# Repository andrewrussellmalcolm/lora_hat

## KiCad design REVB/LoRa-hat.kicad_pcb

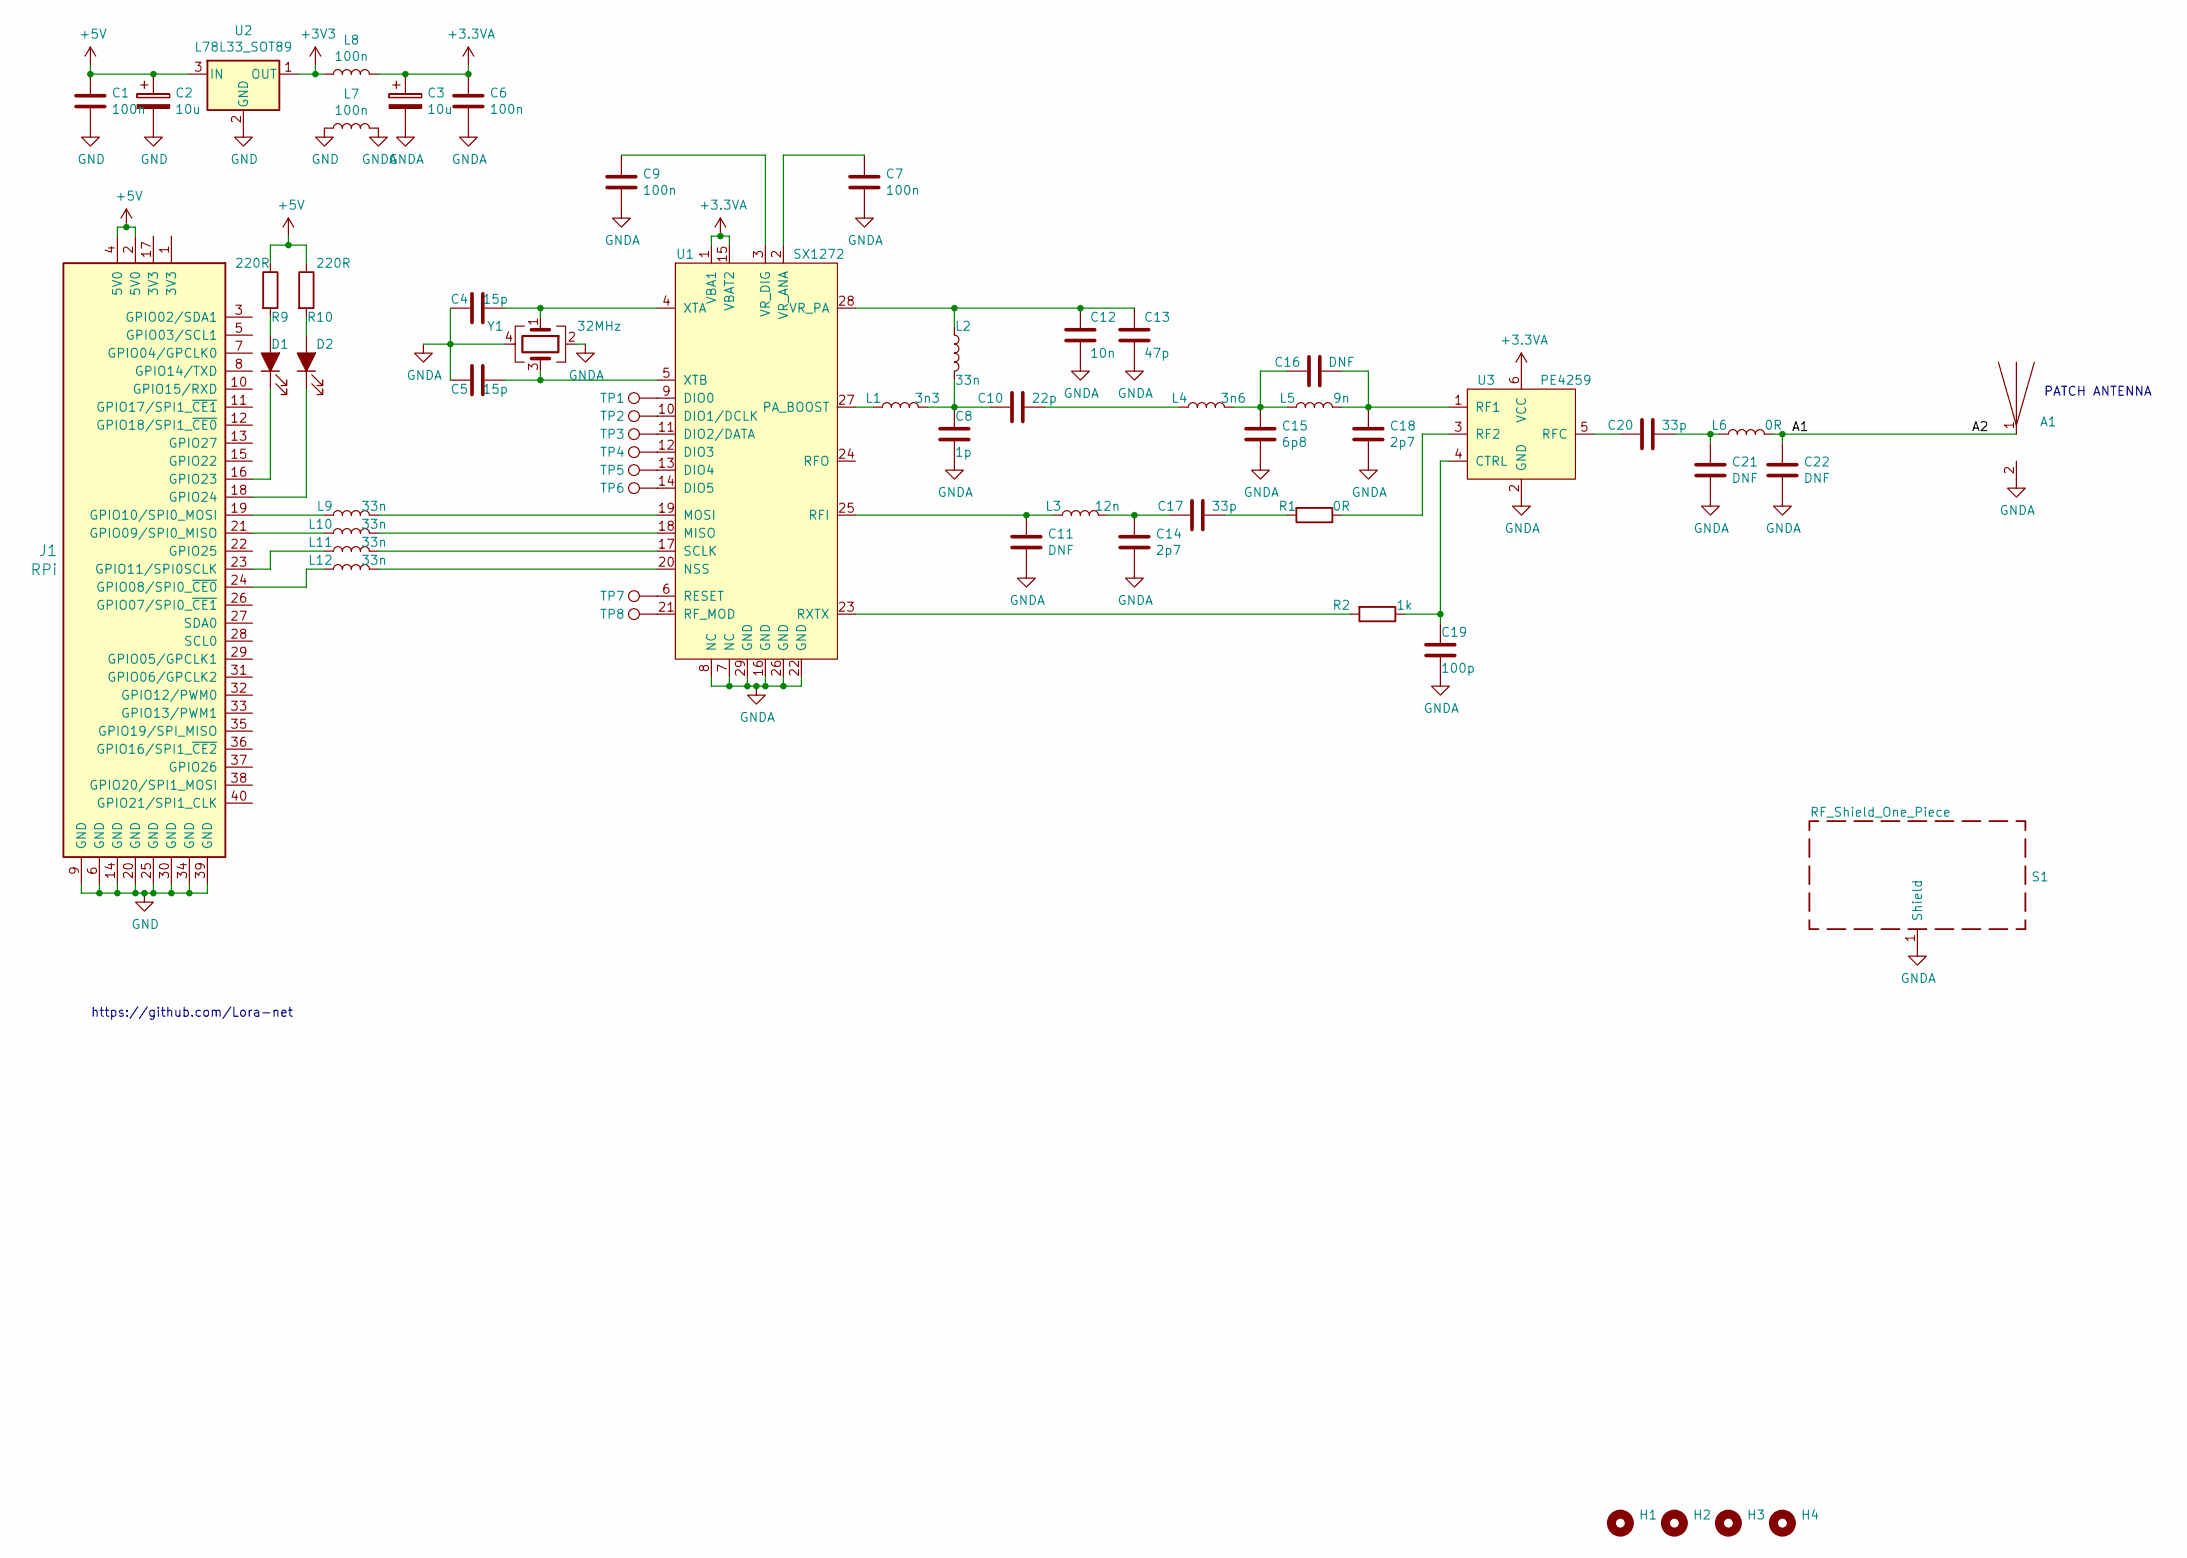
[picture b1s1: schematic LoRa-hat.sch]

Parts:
A1: F-ANTENNA-868MHz
C1, C6, C7, C9: 100n; C_0603_1608Metric
C2, C3: 10u; CP_EIA-3216-10_Kemet-I
C4, C5: 15p; C_0603_1608Metric
C8: 1p; C_0603_1608Metric
C10: 22p; C_0603_1608Metric
C11, C16, C21, C22: DNF; C_0603_1608Metric
C12: 10n; C_0603_1608Metric
C13: 47p; C_0603_1608Metric
C14, C18: 2p7; C_0603_1608Metric
C15: 6p8; C_0603_1608Metric
C17, C20: 33p; C_0603_1608Metric
C19: 100p; C_0603_1608Metric
D1, D2: LED_ALT; LED_LH_R974
H1, H2, H3, H4: Mechanical_Mounting_Hole; Mounting_hole_2.5mm
J1: RPi; PinSocket_2x20_P2.54mm_Vertical
L1: 3n3; L_0603_1608Metric
L2, L9, L10, L11, L12: 33n; L_0603_1608Metric
L3: 12n; L_0603_1608Metric
L4: 3n6; L_0603_1608Metric
L5: 9n; L_0603_1608Metric
L6: 0R; L_0603_1608Metric
L7, L8: 100n; L_0603_1608Metric
R1: 0R; R_0603_1608Metric
R2: 1k; R_0603_1608Metric
R9, R10: 220R; R_0603_1608Metric
S1: RF_Shield_One_Piece; MS256-10S
TP1, TP2, TP3, TP4, TP5, TP6, TP7, TP8: TestPoint; TestPoint_Pad_D1.0mm
U1: SX1272; QFN-28-1EP_6x6mm_P0.65mm_EP4.25x4.25mm_ThermalVias
U2: L78L33_SOT89; SOT-89-3
U3: PE4259; SC70-6
Y1: 32MHz; Crystal_SMD_2016-4Pin_2.0x1.6mm

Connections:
+3.3VA: C3.1, C6.1, L8.2, U1.1 (VBA1), U1.15 (VBAT2), U3.6 (VCC)
+3V3: L8.1, U2.1 (OUT)
+5V: C1.1, C2.1, J1.2 (5V0), J1.4 (5V0), R9.1, R10.1, U2.3 (IN)
/A1: A1.1, C22.1, L6.2
GND: C1.2, C2.2, J1.6 (GND), J1.9 (GND), J1.14 (GND), J1.20 (GND), J1.25 (GND), J1.30 (GND), J1.34 (GND), J1.39 (GND), L7.1, U2.2 (GND)
GNDA: A1.2, C3.2, C4.2, C5.2, C6.2, C7.2, C8.2, C9.2, C11.2, C12.2, C13.2, C14.2, C15.2, C18.2, C19.2, C21.2, C22.2, L7.2, S1.1, U1.7 (NC), U1.8 (NC), U1.16 (GND), U1.22 (GND), U1.26 (GND), U1.29 (GND), U3.2 (GND), Y1.2, Y1.4
unnamed: C4.1, U1.4 (XTA), Y1.1
unnamed: C5.1, U1.5 (XTB), Y1.3
unnamed: C7.1, U1.2 (VR_ANA)
unnamed: C9.1, U1.3 (VR_DIG)
unnamed: C10.1, L4.1
unnamed: C8.1, C10.2, L1.2, L2.2
unnamed: C11.1, L3.1, U1.25 (RFI)
unnamed: C12.1, C13.1, L2.1, U1.28 (VR_PA)
unnamed: C14.1, C17.2, L3.2
unnamed: C15.1, C16.2, L4.2, L5.1
unnamed: C16.1, C18.1, L5.2, U3.1 (RF1)
unnamed: C17.1, R1.2
unnamed: C19.1, R2.1, U3.4 (CTRL)
unnamed: C20.1, C21.1, L6.1
unnamed: C20.2, U3.5 (RFC)
unnamed: D1.1 (K), J1.16 (GPIO23)
unnamed: D1.2 (A), R9.2
unnamed: D2.1 (K), J1.18 (GPIO24)
unnamed: D2.2 (A), R10.2
unnamed: J1.19 (GPIO10/SPI0_MOSI), L9.1
unnamed: J1.21 (GPIO09/SPI0_MISO), L10.1
unnamed: J1.23 (GPIO11/SPI0SCLK), L11.1
unnamed: J1.24 (GPIO08/SPI0_~CE0), L12.1
unnamed: L1.1, U1.27 (PA_BOOST)
unnamed: L9.2, U1.19 (MOSI)
unnamed: L10.2, U1.18 (MISO)
unnamed: L11.2, U1.17 (SCLK)
unnamed: L12.2, U1.20 (NSS)
unnamed: R1.1, U3.3 (RF2)
unnamed: R2.2, U1.23 (RXTX)
unnamed: TP1.1, U1.9 (DIO0)
unnamed: TP2.1, U1.10 (DIO1/DCLK)
unnamed: TP3.1, U1.11 (DIO2/DATA)
unnamed: TP4.1, U1.12 (DIO3)
unnamed: TP5.1, U1.13 (DIO4)
unnamed: TP6.1, U1.14 (DIO5)
unnamed: TP7.1, U1.6 (RESET)
unnamed: TP8.1, U1.21 (RF_MOD)

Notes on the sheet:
https://github.com/Lora-net
PATCH ANTENNA

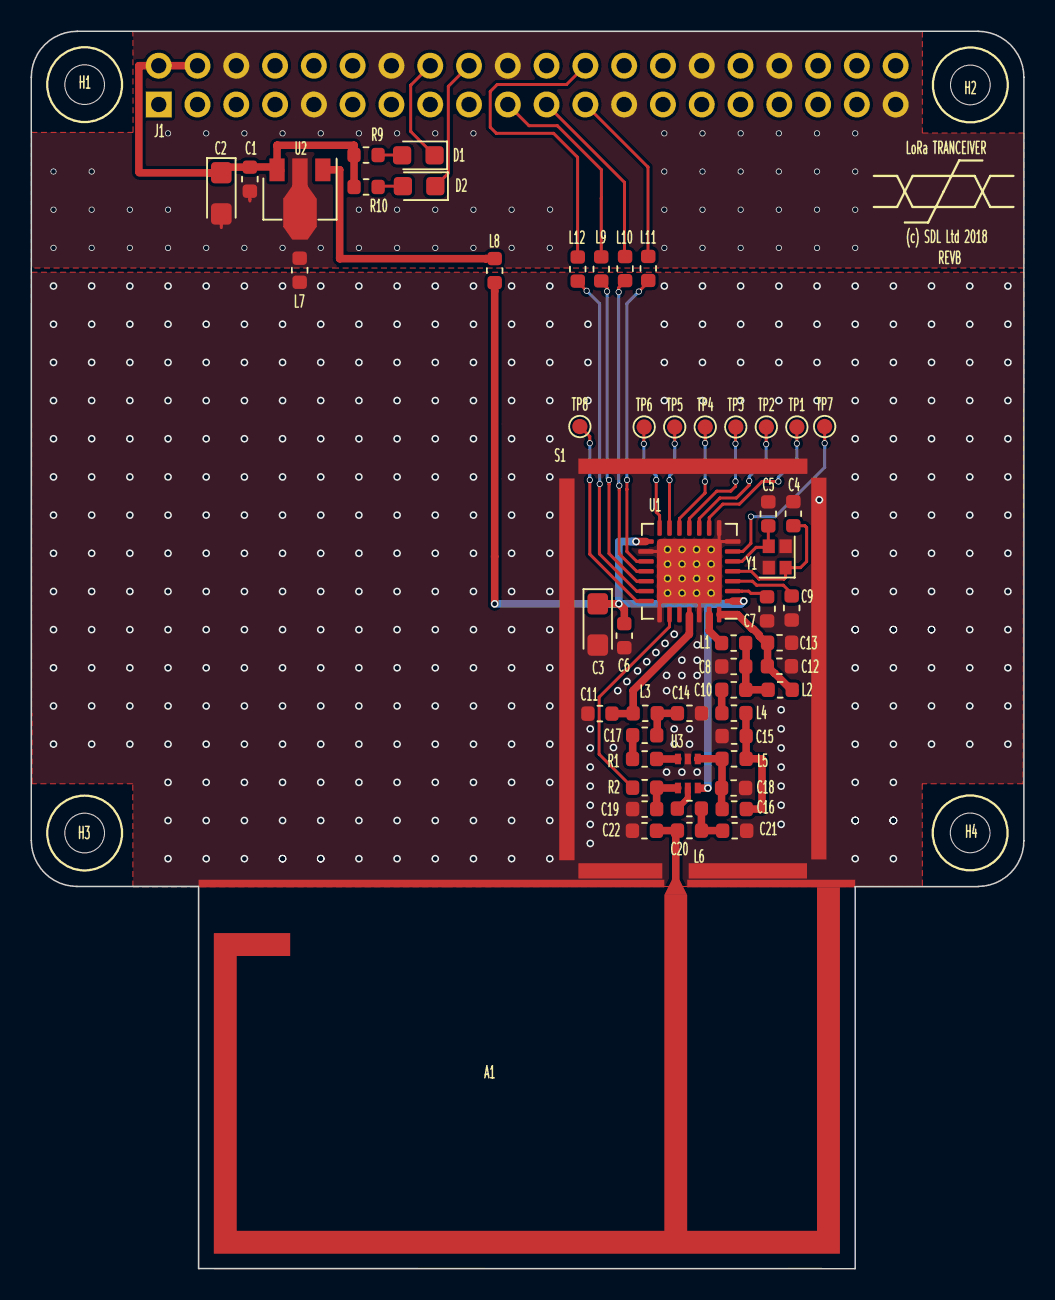
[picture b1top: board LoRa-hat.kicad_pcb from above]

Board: 2 copper layers, 65.0 x 81.0 mm, 60 parts (1 on the bottom side), 44 nets.

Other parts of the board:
(c) SDL Ltd 2018: SDL Logo

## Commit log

2019-08-13 first push of lora project
